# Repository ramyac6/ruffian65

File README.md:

# ruffian65

65% hotswap pcb with encoder, split spacebar support, split and full backspace support, and stepped and regular capslock support

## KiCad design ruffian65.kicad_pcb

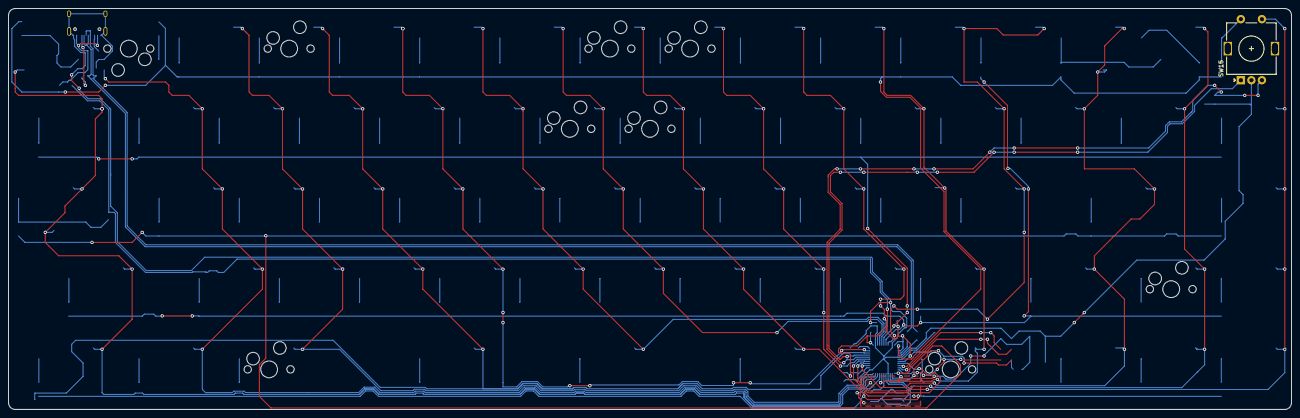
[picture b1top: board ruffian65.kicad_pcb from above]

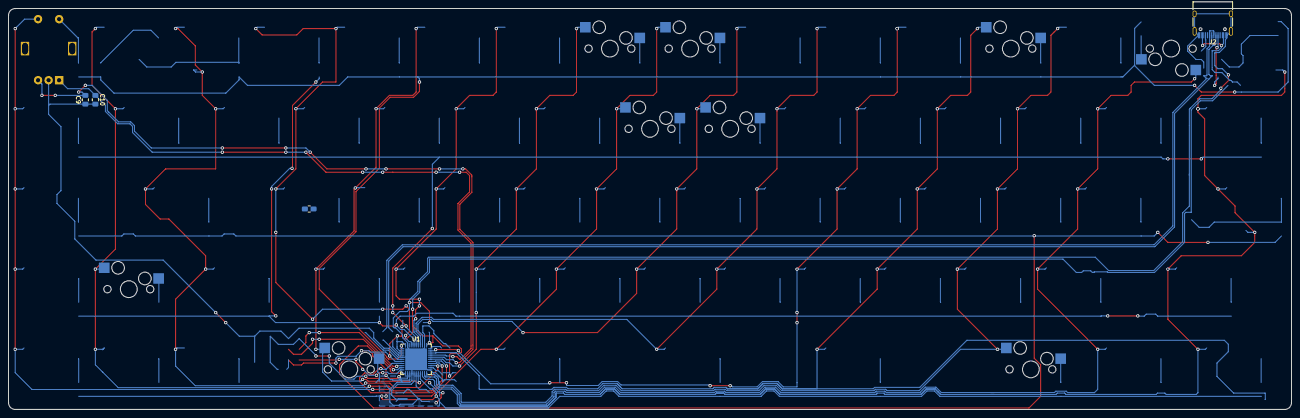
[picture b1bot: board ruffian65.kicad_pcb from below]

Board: 2 copper layers, 304.8 x 95.3 mm, 15 parts (4 on the bottom side), 16 nets.

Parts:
C9, C10: 100nF; C_0805_2012Metric_Pad1.18x1.45mm_HandSolder
J2: USB_C_Receptacle_USB2.0; USB_C_Receptacle_HRO_TYPE-C-31-M-12
SW2: #1; MXOnly-1U-Hotswap
SW4: #3; MXOnly-1U-Hotswap
SW8: #7; MXOnly-1U-Hotswap
SW9: #8; MXOnly-1U-Hotswap
SW15: Rotary_Encoder_Switch; RotaryEncoder_Alps_EC11E-Switch_Vertical_H20mm
SW22: Y; MXOnly-1U-Hotswap
SW23: U; MXOnly-1U-Hotswap
SW42: '; MXOnly-1U-Hotswap
SW58: UP; MXOnly-1U-Hotswap
SW62: LALT; MXOnly-1.5U-Hotswap
SW66: FN; MXOnly-1.5U-Hotswap
U1: ATmega32U4-MU; QFN-44-1EP_7x7mm_P0.5mm_EP5.2x5.2mm

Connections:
+5V: SW42.1, U1.2, U1.7, U1.14, U1.24, U1.34, U1.44
DN: J2.A7, J2.B7
DP: J2.A6, J2.B6
GND: C9.1, C10.2, J2.A1, J2.A12, J2.B1, J2.B12, J2.S1, SW15.C, SW42.2, U1.5, U1.15, U1.23, U1.35, U1.43, U1.45
VCC: J2.A4, J2.A9, J2.B4, J2.B9
col1: SW2.2, U1.21
col2: SW62.2, U1.22
col3: SW4.2, U1.31
col6: SW22.2, U1.36
col7: SW8.2, SW23.2, U1.8
col8: SW9.2, U1.28
col10: SW66.2, U1.18
col13: SW58.2, U1.26
col14: SW15.S1, U1.27
rot0: C9.2, SW15.B, U1.29
rot1: C10.1, SW15.A, U1.30

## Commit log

2021-09-06 Initialize project
2021-09-06 added submodules
2021-09-06 Added symbol and footprint libraries
2021-09-06 Finished matrix
2021-09-07 wired differential
2021-09-11 wiring done?
2021-09-11 wiring finished
2021-09-11 small track fix
2021-09-12 added ec11
2021-09-13 encoder support?
2021-09-13 added all the supports
2021-12-05 added image
